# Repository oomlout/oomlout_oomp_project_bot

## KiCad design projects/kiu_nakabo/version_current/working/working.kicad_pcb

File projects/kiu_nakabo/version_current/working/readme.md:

# nakabo by kiu  
This is a harvested standardized copy of a project from github.  
The original project can be found at:  
https://github.com/kiu/nakabo  
Please consult that link for additional, details, files, and license information.  
Note: It was auto harvested and if the original repo had more than one board file or anything out of the ordinary the files here are likely not representative.

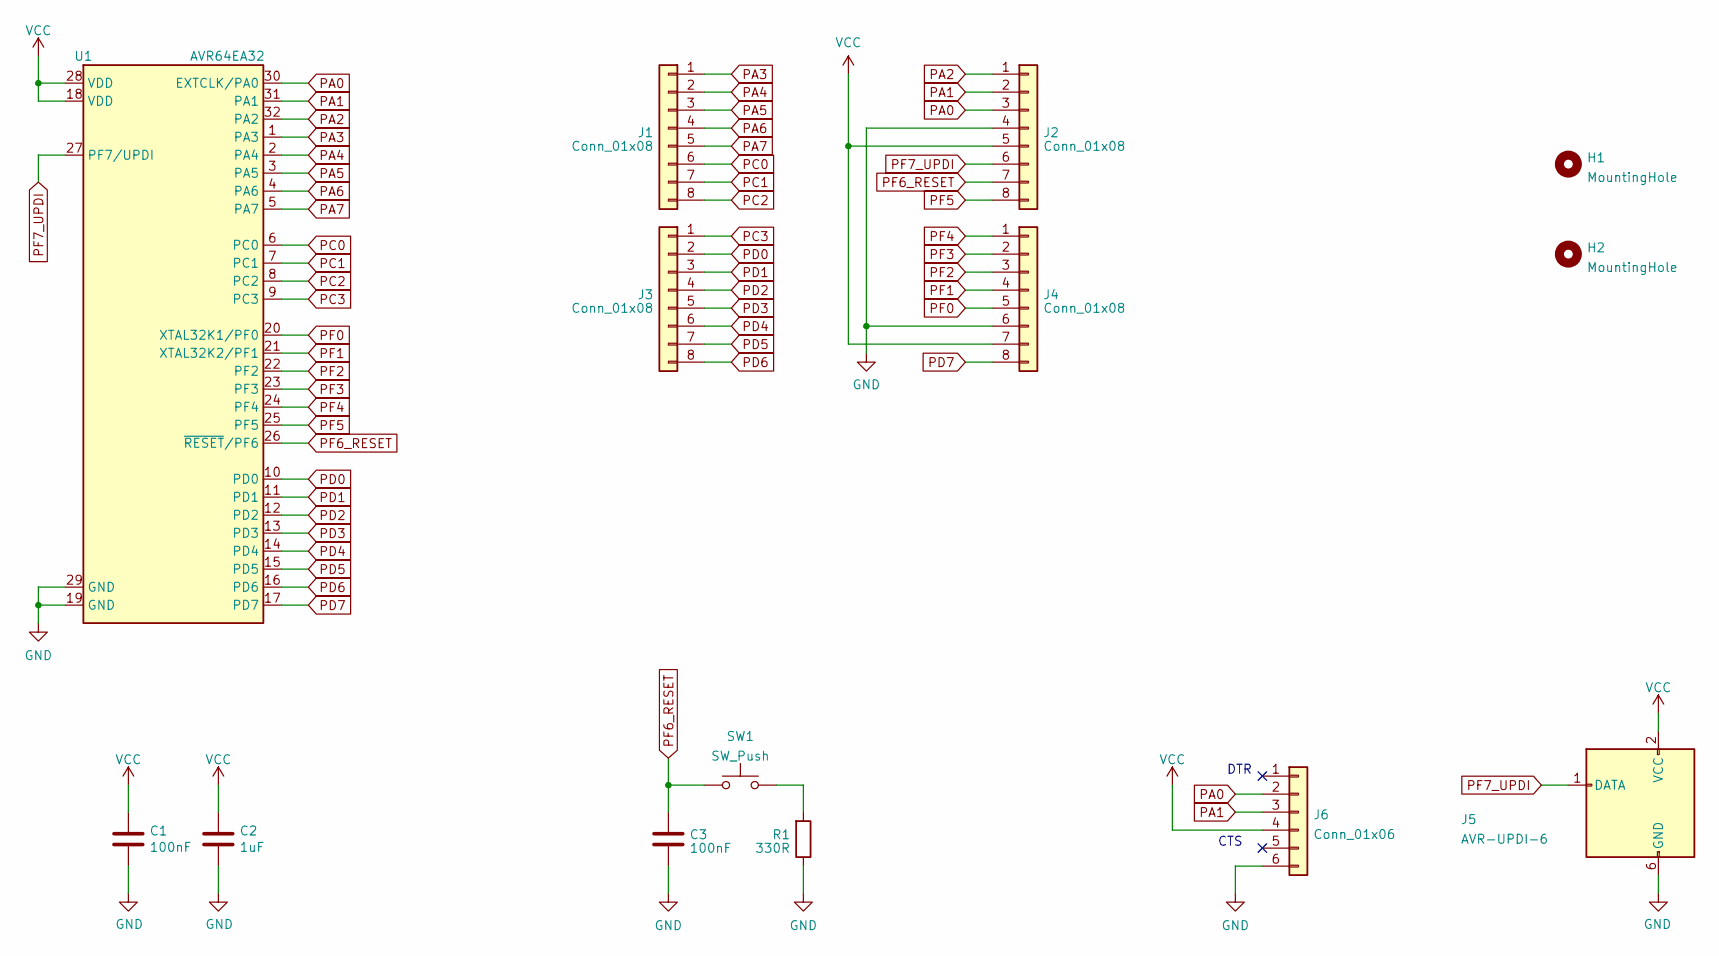
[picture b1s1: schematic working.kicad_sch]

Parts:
C1, C3: 100nF; C_0805_2012Metric
C2: 1uF; C_0805_2012Metric
H1, H2: MountingHole; MountingHole_3.2mm_M3_DIN965
J1, J2, J3, J4: Conn_01x08; PinSocket_1x08_P2.54mm_Vertical
J5: AVR-UPDI-6; IDC-Header_2x03_P2.54mm_Vertical
J6: Conn_01x06; PinSocket_1x06_P2.54mm_Vertical
R1: 330R; R_0805_2012Metric
SW1: SW_Push; SW_Push_1P1T_NO_4.5x4.5mm
U1: AVR64EA32; TQFP-32_7x7mm_P0.8mm

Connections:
GND: C1.2, C2.2, C3.2, J2.4, J4.6, J5.6 (GND), J6.6, R1.1, U1.19 (GND), U1.29 (GND)
unnamed: R1.2, SW1.2
PA0: J2.3, J6.2, U1.30 (EXTCLK/PA0)
PA1: J2.2, J6.3, U1.31 (PA1)
PA2: J2.1, U1.32 (PA2)
PA3: J1.1, U1.1 (PA3)
PA4: J1.2, U1.2 (PA4)
PA5: J1.3, U1.3 (PA5)
PA6: J1.4, U1.4 (PA6)
PA7: J1.5, U1.5 (PA7)
PC0: J1.6, U1.6 (PC0)
PC1: J1.7, U1.7 (PC1)
PC2: J1.8, U1.8 (PC2)
PC3: J3.1, U1.9 (PC3)
PD0: J3.2, U1.10 (PD0)
PD1: J3.3, U1.11 (PD1)
PD2: J3.4, U1.12 (PD2)
PD3: J3.5, U1.13 (PD3)
PD4: J3.6, U1.14 (PD4)
PD5: J3.7, U1.15 (PD5)
PD6: J3.8, U1.16 (PD6)
PD7: J4.8, U1.17 (PD7)
PF0: J4.5, U1.20 (XTAL32K1/PF0)
PF1: J4.4, U1.21 (XTAL32K2/PF1)
PF2: J4.3, U1.22 (PF2)
PF3: J4.2, U1.23 (PF3)
PF4: J4.1, U1.24 (PF4)
PF5: J2.8, U1.25 (PF5)
PF6_RESET: C3.1, J2.7, SW1.1, U1.26 (~RESET/PF6)
PF7_UPDI: J2.6, J5.1 (DATA), U1.27 (PF7/UPDI)
VCC: C1.1, C2.1, J2.5, J4.7, J5.2 (VCC), J6.4, U1.18 (VDD), U1.28 (VDD)

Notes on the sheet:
DTR
CTS

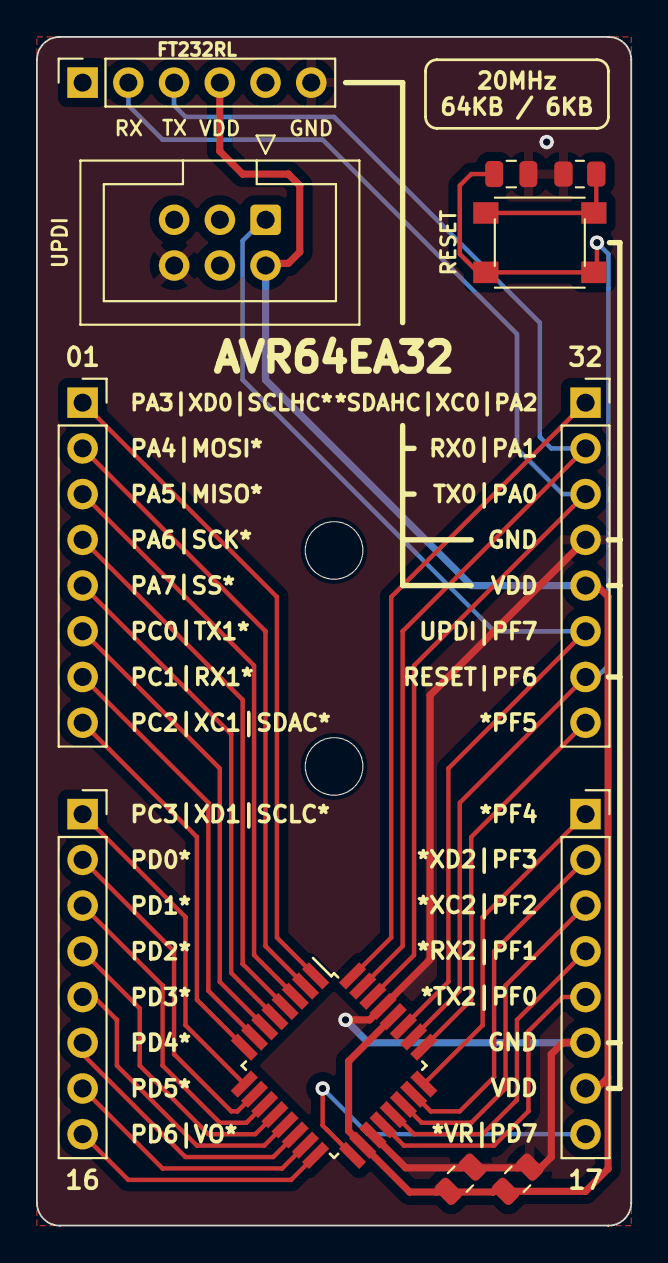
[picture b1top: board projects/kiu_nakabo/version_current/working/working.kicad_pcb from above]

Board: 2 copper layers, 33.0 x 66.0 mm, 14 parts (0 on the bottom side), 31 nets.

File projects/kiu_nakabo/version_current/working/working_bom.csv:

"Id";"Designator";"Footprint";"Quantity";"Designation";"Supplier and ref";
1;"J1,J4,J3,J2";"PinSocket_1x08_P2.54mm_Vertical";4;"Conn_01x08";;;
2;"J5";"IDC-Header_2x03_P2.54mm_Vertical";1;"AVR-UPDI-6";;;
3;"C2";"C_0805_2012Metric";1;"1uF";;;
4;"C3,C1";"C_0805_2012Metric";2;"100nF";;;
5;"H1,H2";"MountingHole_3.2mm_M3_DIN965";2;"MountingHole";;;
6;"U1";"TQFP-32_7x7mm_P0.8mm";1;"AVR64EA32";;;
7;"SW1";"SW_Push_1P1T_NO_4.5x4.5mm";1;"SW_Push";;;
8;"J6";"PinSocket_1x06_P2.54mm_Vertical";1;"Conn_01x06";;;
9;"R1";"R_0805_2012Metric";1;"330R";;;

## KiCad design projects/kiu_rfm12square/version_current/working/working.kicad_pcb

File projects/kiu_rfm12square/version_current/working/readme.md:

# rfm12square by kiu  
This is a harvested standardized copy of a project from github.  
The original project can be found at:  
https://github.com/kiu/rfm12square  
Please consult that link for additional, details, files, and license information.  
Note: It was auto harvested and if the original repo had more than one board file or anything out of the ordinary the files here are likely not representative.

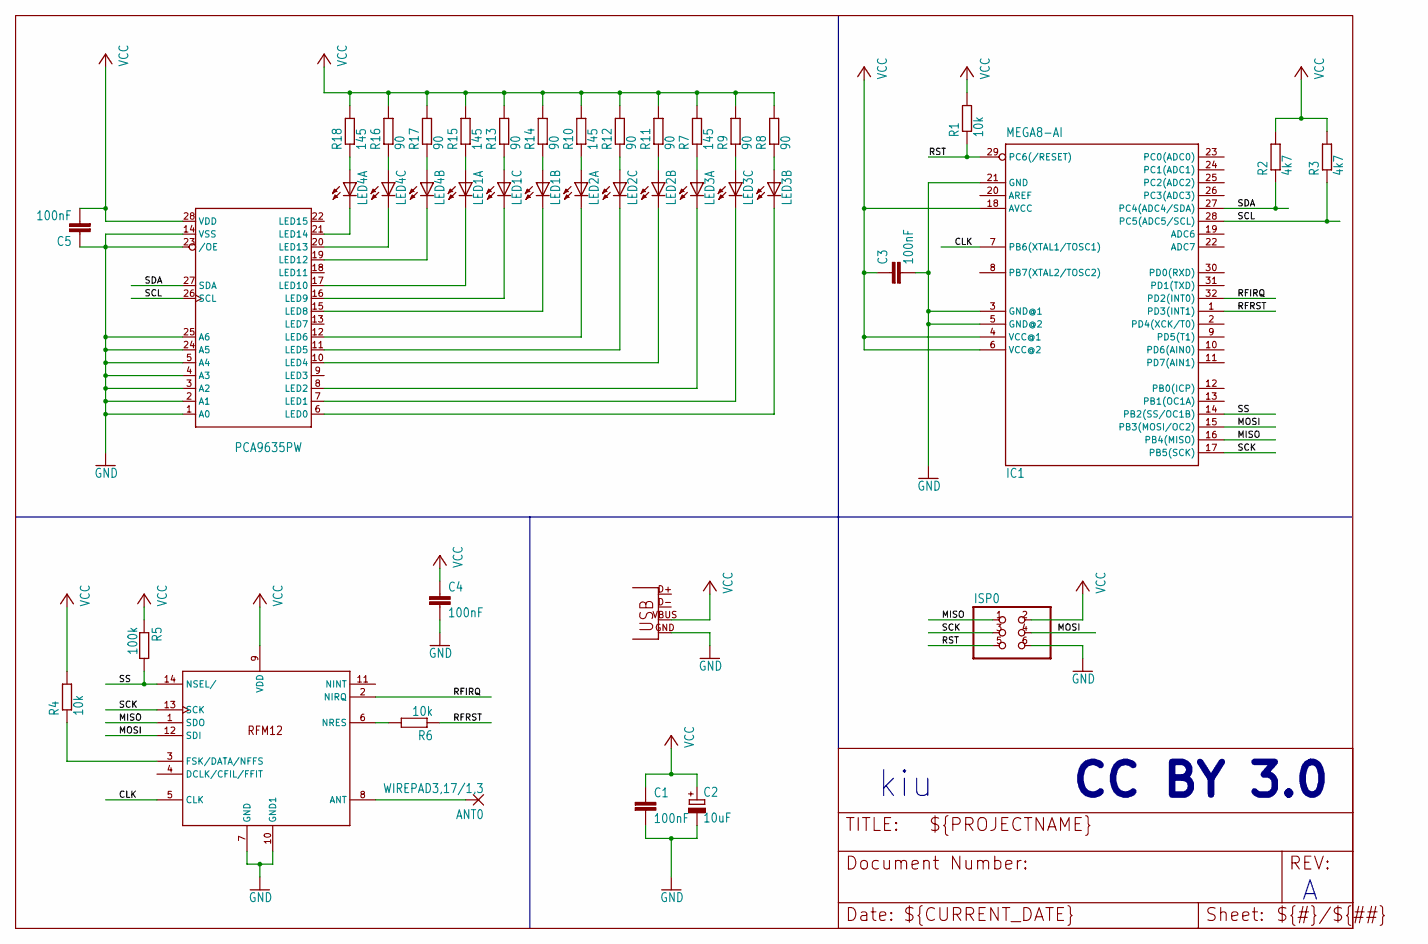
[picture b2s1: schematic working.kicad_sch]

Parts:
ANT0: WIREPAD3,17/1,3; 3,17_1,3
C1, C3, C4, C5: 100nF; C0603
C2: 10uF; CT3216
IC1: MEGA8-AI; TQFP32-08
IC2: PCA9635PW; TSSOP28
ISP0: PINHD-2X3; 2X03
LED1, LED2, LED3, LED4: MULTILED_LRTB_G6TG; P-LCC-6_TOPLED
R1, R4, R6: 10k; R0603
R2, R3: 4k7; R0603
R5: 100k; R0603
R7, R10, R15, R18: 145; R0603
R8, R9, R11, R12, R13, R14, R16, R17: 90; R0603
U$1: FRM12; RFM12
X1: USB-MICROB

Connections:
CLK: IC1.7 (PB6(XTAL1/TOSC1)), U$1.5 (CLK)
GND: C1.2, C2.-, C3.2, C4.2, C5.1, IC1.3 (GND@1), IC1.5 (GND@2), IC1.21 (GND), IC2.1 (A0), IC2.2 (A1), IC2.3 (A2), IC2.4 (A3), IC2.5 (A4), IC2.14 (VSS), IC2.23 (/OE), IC2.24 (A5), IC2.25 (A6), ISP0.6, U$1.7 (GND), U$1.10 (GND1), X1.GND
MISO: IC1.16 (PB4(MISO)), ISP0.1, U$1.1 (SDO)
MOSI: IC1.15 (PB3(MOSI/OC2)), ISP0.4, U$1.12 (SDI)
unnamed: LED4.A2 (A), R17.1
unnamed: LED1.A2 (A), R14.1
unnamed: LED4.A3 (A), R16.1
unnamed: LED4.A1 (A), R18.1
unnamed: LED1.A3 (A), R13.1
unnamed: IC2.6 (LED0), LED3.C2 (C)
unnamed: IC2.7 (LED1), LED3.C3 (C)
unnamed: IC2.8 (LED2), LED3.C1 (C)
unnamed: IC2.10 (LED4), LED2.C2 (C)
unnamed: IC2.11 (LED5), LED2.C3 (C)
unnamed: IC2.12 (LED6), LED2.C1 (C)
unnamed: IC2.15 (LED8), LED1.C2 (C)
unnamed: R4.1, U$1.3 (FSK/DATA/NFFS)
unnamed: R6.2, U$1.6 (NRES)
unnamed: LED1.A1 (A), R15.1
unnamed: ANT0.1, U$1.8 (ANT)
unnamed: IC2.16 (LED9), LED1.C3 (C)
unnamed: IC2.17 (LED10), LED1.C1 (C)
unnamed: LED2.A3 (A), R12.1
unnamed: IC2.19 (LED12), LED4.C2 (C)
unnamed: IC2.20 (LED13), LED4.C3 (C)
unnamed: IC2.21 (LED14), LED4.C1 (C)
unnamed: LED2.A2 (A), R11.1
unnamed: LED2.A1 (A), R10.1
unnamed: LED3.A1 (A), R7.1
unnamed: LED3.A3 (A), R9.1
unnamed: LED3.A2 (A), R8.1
RFIRQ: IC1.32 (PD2(INT0)), U$1.2 (NIRQ)
RFRST: IC1.1 (PD3(INT1)), R6.1
RST: IC1.29 (PC6(/RESET)), ISP0.5, R1.1
SCK: IC1.17 (PB5(SCK)), ISP0.3, U$1.13 (SCK)
SCL: IC1.28 (PC5(ADC5/SCL)), IC2.26 (SCL), R3.1
SDA: IC1.27 (PC4(ADC4/SDA)), IC2.27 (SDA), R2.1
SS: IC1.14 (PB2(SS/OC1B)), R5.2, U$1.14 (NSEL/)
VCC: C1.1, C2.+, C3.1, C4.1, C5.2, IC1.4 (VCC@1), IC1.6 (VCC@2), IC1.18 (AVCC), IC2.28 (VDD), ISP0.2, R1.2, R2.2, R3.2, R4.2, R5.1, R7.2, R8.2, R9.2, R10.2, R11.2, R12.2, R13.2, R14.2, R15.2, R16.2, R17.2, R18.2, U$1.9 (VDD), X1.VBUS

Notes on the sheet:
CC BY 3.0
kiu

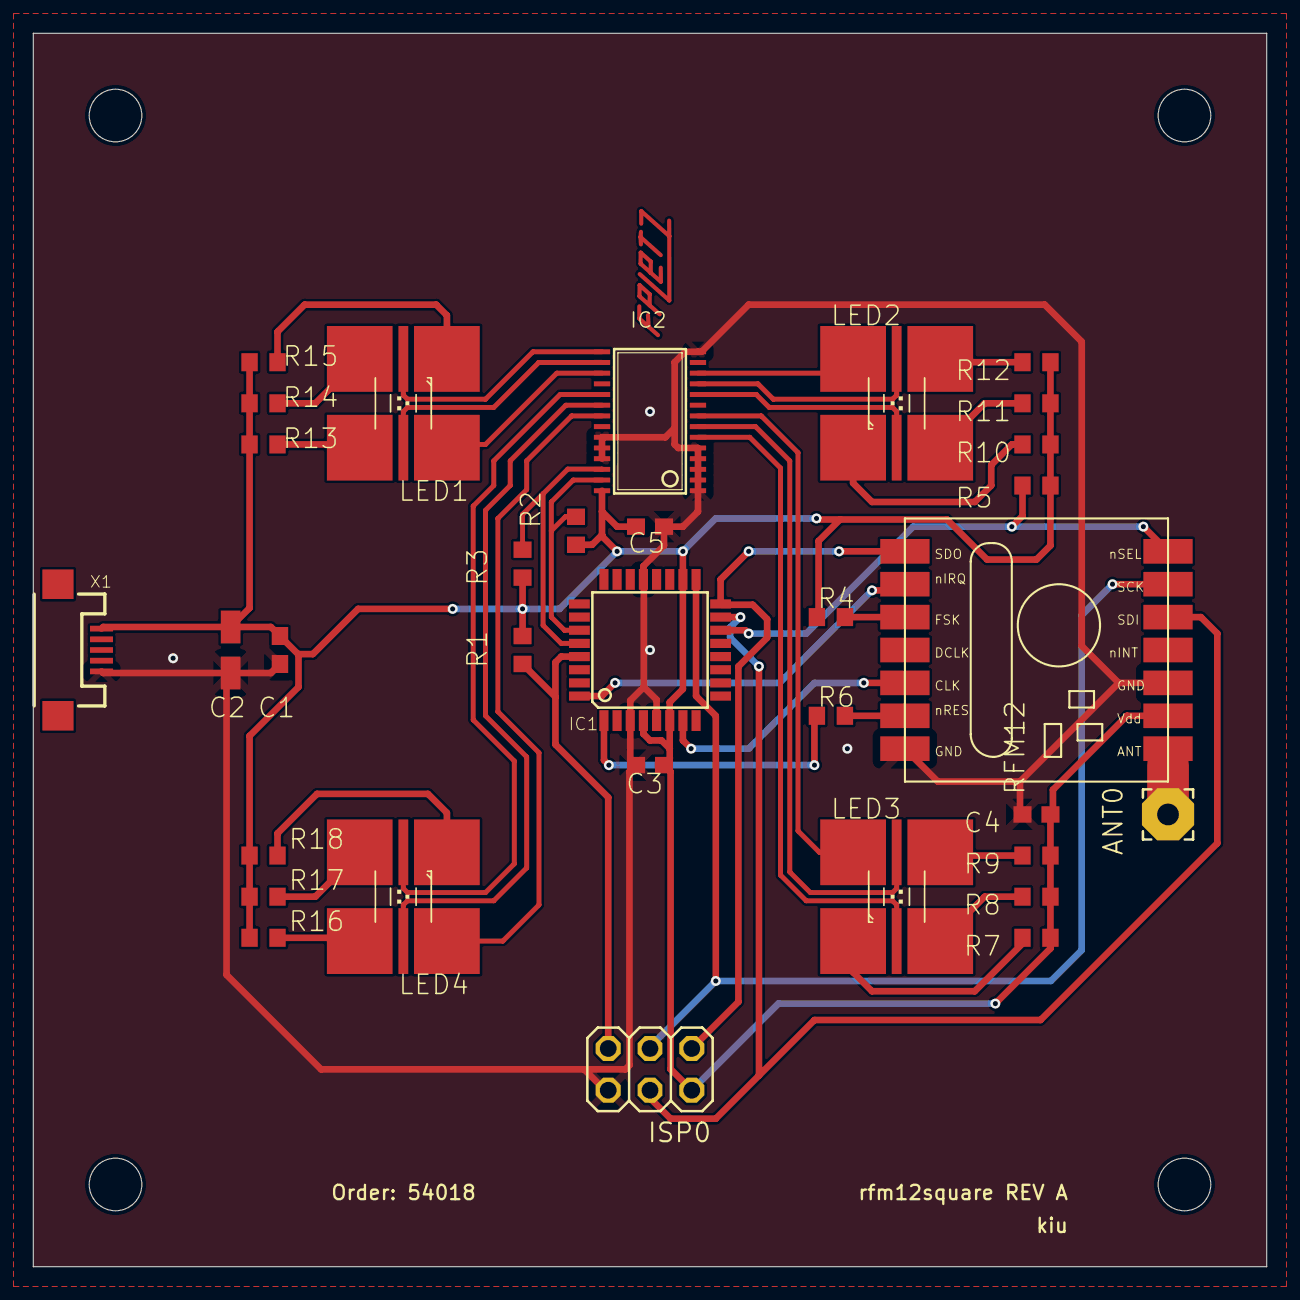
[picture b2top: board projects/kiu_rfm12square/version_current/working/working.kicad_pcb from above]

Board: 2 copper layers, 75.0 x 75.0 mm, 37 parts (0 on the bottom side), 39 nets.

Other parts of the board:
@HOLE0, @HOLE1, @HOLE2, @HOLE3: (no value)

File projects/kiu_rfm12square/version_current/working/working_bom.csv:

"Id";"Designator";"Footprint";"Quantity";"Designation";"Supplier and ref";
1;"@HOLE2,@HOLE1,@HOLE3,@HOLE0";"";4;"";;;
2;"LED1,LED3,LED4,LED2";"P-LCC-6_TOPLED";4;"MULTILED_LRTB_G6TG";;;
3;"R7,R18,R15,R10";"R0603";4;"145";;;
4;"C5,C3,C1,C4";"C0603";4;"100nF";;;
5;"R1,R6,R4";"R0603";3;"10k";;;
6;"R3,R2";"R0603";2;"4k7";;;
7;"U$1";"RFM12";1;"FRM12";;;
8;"ISP0";"2X03";1;"";;;
9;"IC2";"TSSOP28";1;"PCA9635PW";;;
10;"R14,R17,R11,R12,R13,R9,R16,R8";"R0603";8;"90";;;
11;"X1";"USB-MICROB";1;"USB-MICROB";;;
12;"R5";"R0603";1;"100k";;;
13;"IC1";"TQFP32-08";1;"MEGA8-AI";;;
14;"C2";"CT3216";1;"10uF";;;
15;"ANT0";"3,17_1,3";1;"WIREPAD3,17/1,3";;;

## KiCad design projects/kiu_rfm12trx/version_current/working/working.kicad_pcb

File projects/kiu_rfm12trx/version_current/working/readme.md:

# rfm12trx by kiu  
This is a harvested standardized copy of a project from github.  
The original project can be found at:  
https://github.com/kiu/rfm12trx  
Please consult that link for additional, details, files, and license information.  
Note: It was auto harvested and if the original repo had more than one board file or anything out of the ordinary the files here are likely not representative.

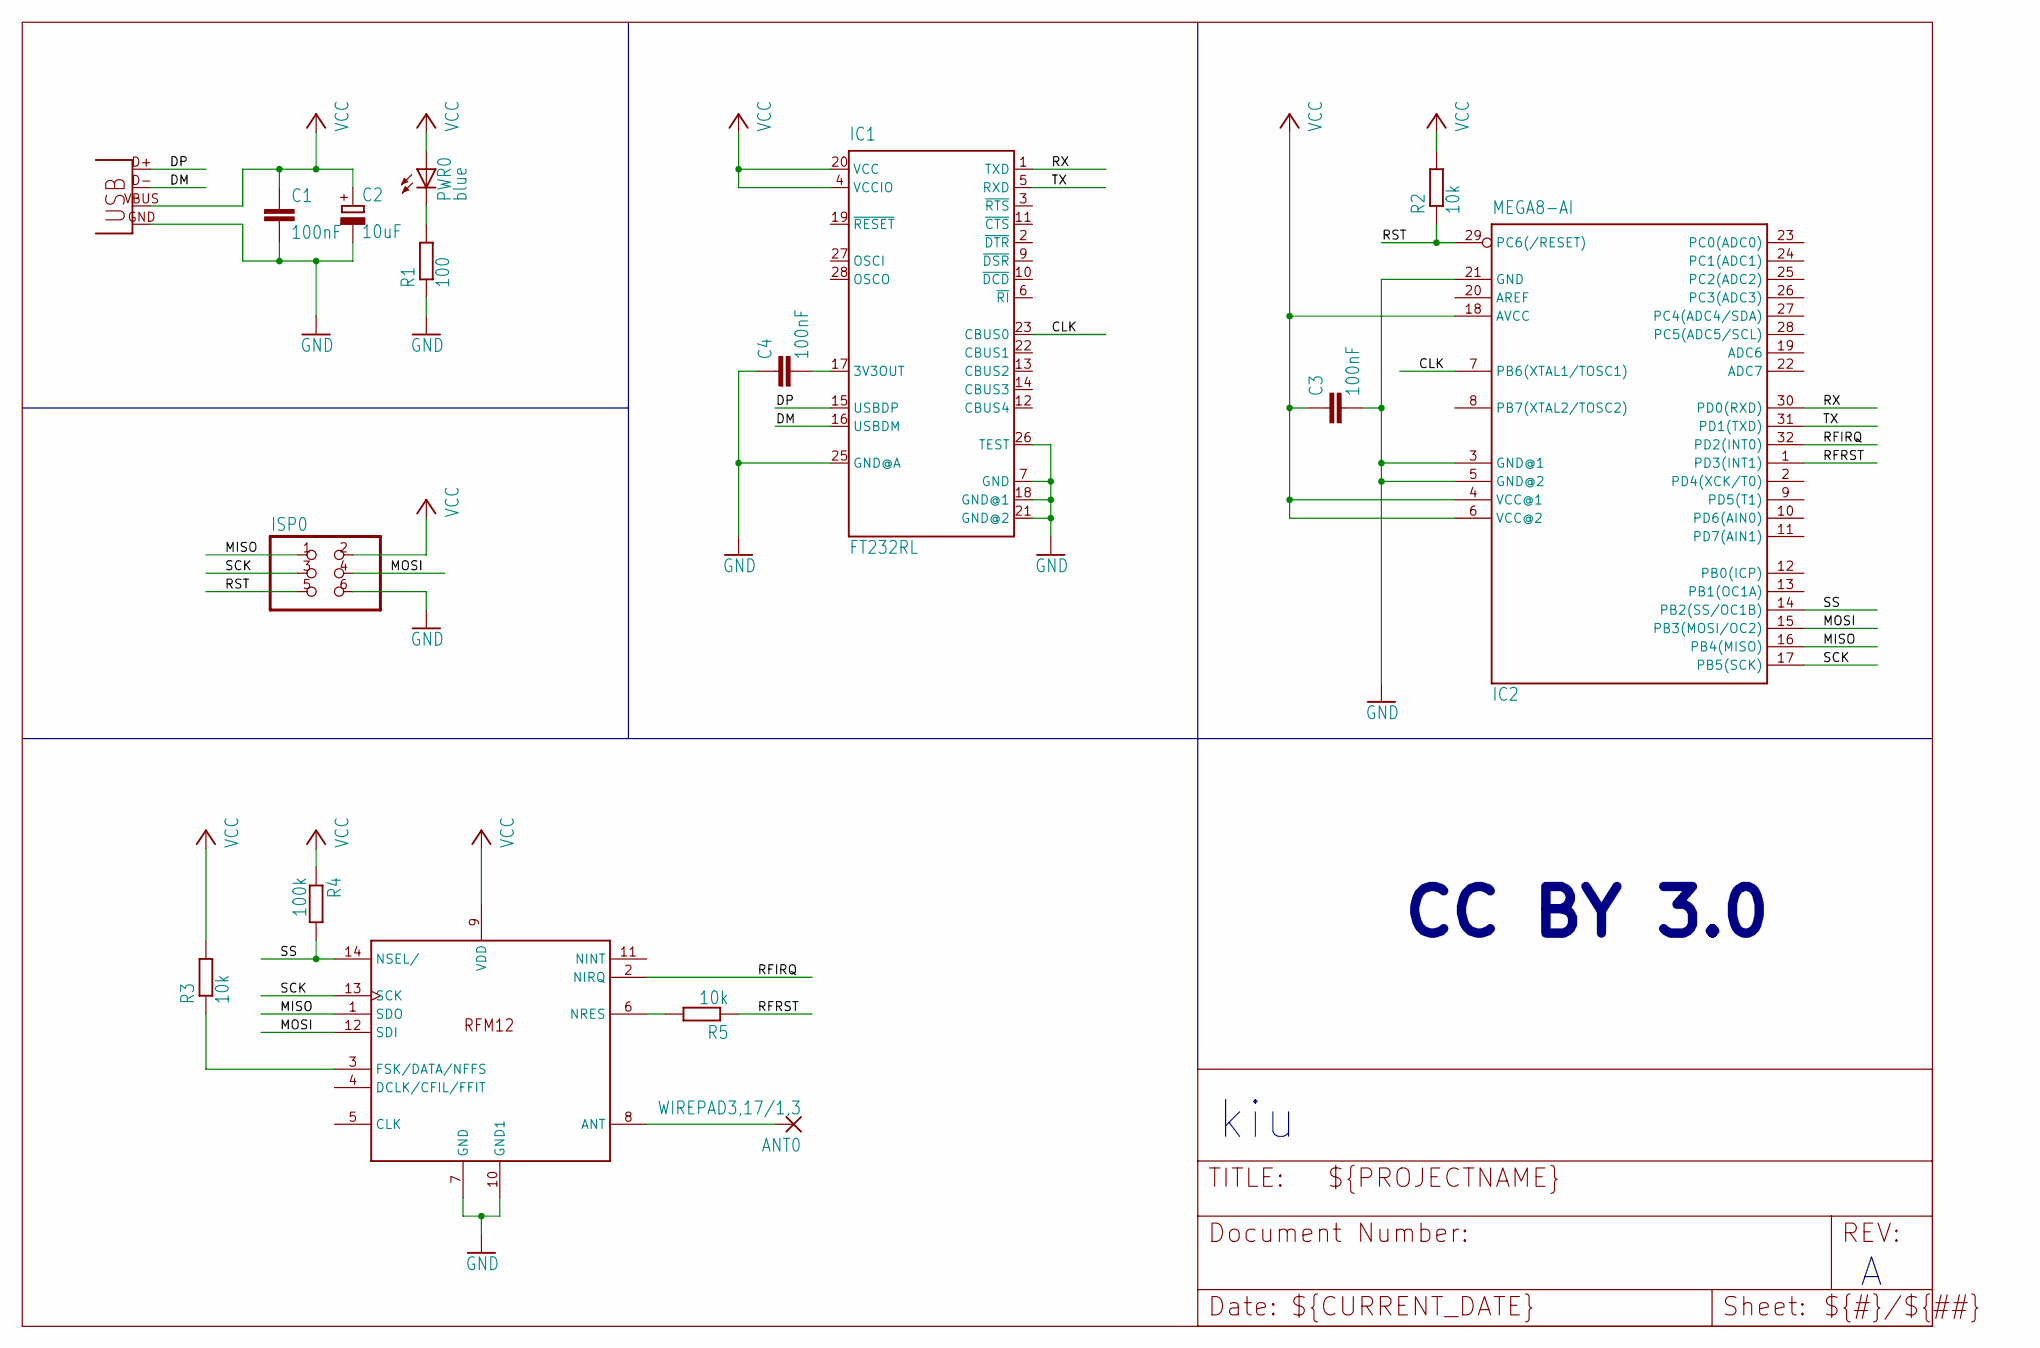
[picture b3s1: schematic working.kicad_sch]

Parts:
ANT0: WIREPAD3,17/1,3; 3,17_1,3
C1, C3, C4: 100nF; C0603
C2: 10uF; CT3216
IC1: FT232RL; SSOP28
IC2: MEGA8-AI; TQFP32-08
ISP0: PINHD-2X3; 2X03
PWR0: blue; CHIP-LED0805
R1: 100; R0603
R2, R3, R5: 10k; R0603
R4: 100k; R0603
U$1: FRM12; RFM12
X1: USB-MICROB

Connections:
CLK: IC1.23 (CBUS0), IC2.7 (PB6(XTAL1/TOSC1))
DM: IC1.16 (USBDM), X1.D-
DP: IC1.15 (USBDP), X1.D+
GND: C1.2, C2.-, C3.2, C4.1, IC1.7 (GND), IC1.18 (GND@1), IC1.21 (GND@2), IC1.25 (GND@A), IC1.26 (TEST), IC2.3 (GND@1), IC2.5 (GND@2), IC2.21 (GND), ISP0.6, R1.1, U$1.7 (GND), U$1.10 (GND1), X1.GND
MISO: IC2.16 (PB4(MISO)), ISP0.1, U$1.1 (SDO)
MOSI: IC2.15 (PB3(MOSI/OC2)), ISP0.4, U$1.12 (SDI)
unnamed: PWR0.C, R1.2
unnamed: C4.2, IC1.17 (3V3OUT)
unnamed: R3.1, U$1.3 (FSK/DATA/NFFS)
unnamed: R5.2, U$1.6 (NRES)
unnamed: ANT0.1, U$1.8 (ANT)
RFIRQ: IC2.32 (PD2(INT0)), U$1.2 (NIRQ)
RFRST: IC2.1 (PD3(INT1)), R5.1
RST: IC2.29 (PC6(/RESET)), ISP0.5, R2.1
RX: IC1.1 (TXD), IC2.30 (PD0(RXD))
SCK: IC2.17 (PB5(SCK)), ISP0.3, U$1.13 (SCK)
SS: IC2.14 (PB2(SS/OC1B)), R4.2, U$1.14 (NSEL/)
TX: IC1.5 (RXD), IC2.31 (PD1(TXD))
VCC: C1.1, C2.+, C3.1, IC1.4 (VCCIO), IC1.20 (VCC), IC2.4 (VCC@1), IC2.6 (VCC@2), IC2.18 (AVCC), ISP0.2, PWR0.A, R2.2, R3.2, R4.1, U$1.9 (VDD), X1.VBUS

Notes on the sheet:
kiu
CC BY 3.0

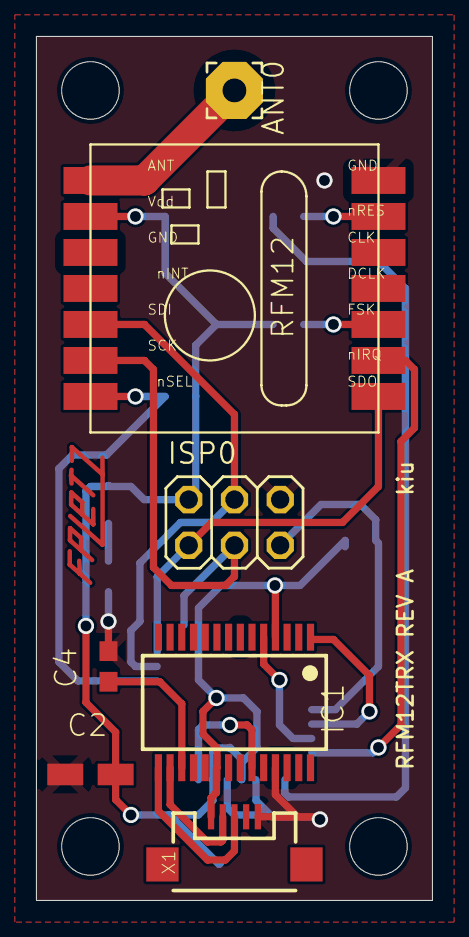
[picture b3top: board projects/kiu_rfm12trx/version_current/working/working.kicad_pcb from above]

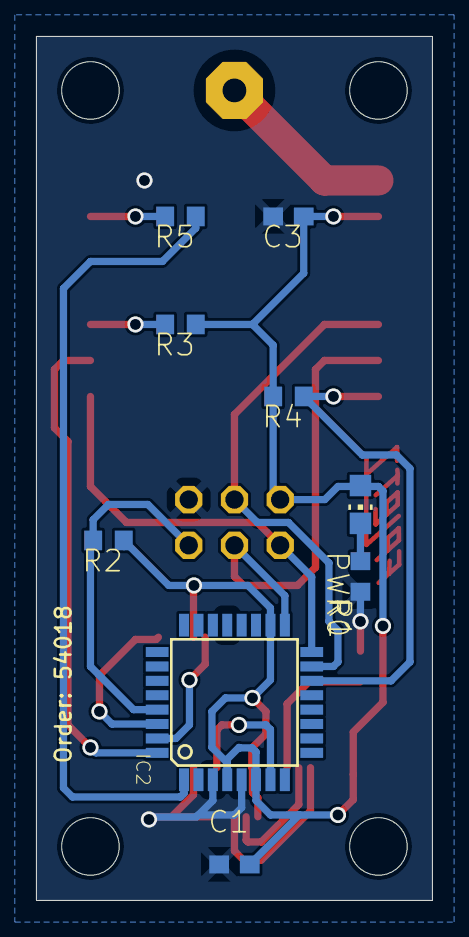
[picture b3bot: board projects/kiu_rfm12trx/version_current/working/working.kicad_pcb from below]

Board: 2 copper layers, 22.0 x 48.0 mm, 20 parts (9 on the bottom side), 19 nets.

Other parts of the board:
@HOLE0, @HOLE1, @HOLE2, @HOLE3: (no value)

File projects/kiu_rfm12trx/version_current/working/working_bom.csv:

"Id";"Designator";"Footprint";"Quantity";"Designation";"Supplier and ref";
1;"X1";"USB-MICROB";1;"USB-MICROB";;;
2;"@HOLE2,@HOLE0,@HOLE1,@HOLE3";"";4;"";;;
3;"C4,C1,C3";"C0603";3;"100nF";;;
4;"IC1";"SSOP28";1;"FT232RL";;;
5;"C2";"CT3216";1;"10uF";;;
6;"ANT0";"3,17_1,3";1;"WIREPAD3,17/1,3";;;
7;"ISP0";"2X03";1;"";;;
8;"U$1";"RFM12";1;"FRM12";;;
9;"R3,R5,R2";"R0603";3;"10k";;;
10;"IC2";"TQFP32-08";1;"MEGA8-AI";;;
11;"R4";"R0603";1;"100k";;;
12;"R1";"R0603";1;"100";;;
13;"PWR0";"CHIP-LED0805";1;"blue";;;

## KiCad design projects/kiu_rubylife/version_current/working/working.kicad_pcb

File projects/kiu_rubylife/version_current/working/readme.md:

# OOMP Project  
## rubylife  by kiu  
  
oomp key: oomp_projects_flat_kiu_rubylife  
(snippet of original readme)  
  
- rubylife  
Show the world your ruby affection and live the [-BadgeLife](https://twitter.com/search?q=%23badgelife)!  

- What does it do?  
Besides being a stylish ruby pin, it can blink a few animations :)  
  
- What do I need?  
All you need is soldering gear (iron, tin, tweezers). Everything else is in the kit.  
  
-- I don't know how to solder!  
It's easier than it looks, but a bit of help to kickstart your hardware adventure doesn't hurt. Ask your colleagues or friends for help. Or seek help in a [hackerspace](https://hackaday.io/hackerspaces) near you, they will love to teach you the ropes!  
  
-- Anything I need to know before I start?  
Be aware that all parts - except for the resistors - have a polarity. Their orientation on the board is important.  
  
Checkout this [reference](https://github.com/kiu/rubylife/raw/master/media/rubylife_polarity.jpg)!  
  
-- What is in the kit?  
  
| Amount | Item |  
| ------ | ---- |  
| 1 | Printed circuit board |  
| 1 | Pre-programmed microcontroller |  
| 8 | Red LED |  
| 8 | Resistors |  
| 1 | Capacitor |  
| 1 | Battery Holder |  
| 1 | Battery |  
| 1 | Mounting pin |  
| 1 | Glue dot |  
  
A more detailed description can be found in the [Bill-Of-Materials](https://github.com/kiu/rubylife/raw/master/bom.pdf)  
  
- I want to write my own software  
Easy, but be aware that you need C skills to proceed :/  
  
1. Setup an ATTiny development environment, e.g. [Atmel Studio](https://www.microchip.co  
  full source readme at [readme_src.md](readme_src.md)  
  
source repo at: [https://github.com/kiu/rubylife](https://github.com/kiu/rubylife)  
## Board  

## Schematic  

[schematic pdf](working_schematic.pdf)  
## Images

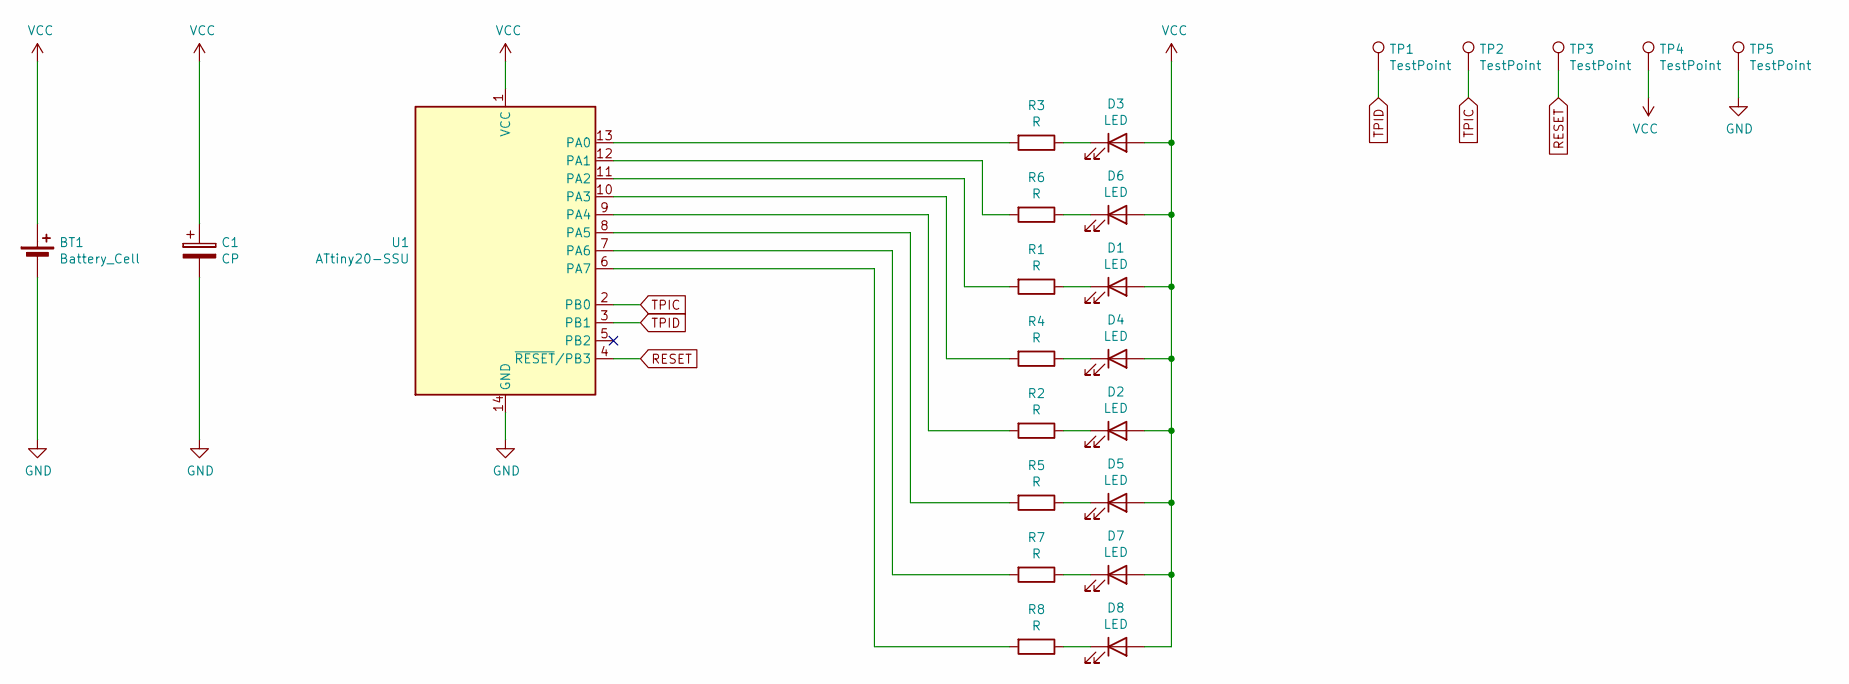
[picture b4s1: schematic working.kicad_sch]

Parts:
BT1: Battery_Cell; CR2032 SMD
C1: CP; CP_Tantalum_Case-B_EIA-3528-21_Hand
D1, D2, D3, D4, D5, D6, D7, D8: LED; LED_1206
R1, R2, R3, R4, R5, R6, R7, R8: R; R_1206
TP1, TP2, TP3, TP4, TP5: TestPoint; Measurement_Point_Round-SMD-Pad_Small
U1: ATtiny20-SSU; SOIC-14_3.9x8.7mm_Pitch1.27mm

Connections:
GND: BT1.2 (-), C1.2, TP5.1, U1.14 (GND)
unnamed: D1.1 (K), R1.1
unnamed: D2.1 (K), R2.1
unnamed: D3.1 (K), R3.1
unnamed: D4.1 (K), R4.1
unnamed: D5.1 (K), R5.1
unnamed: D6.1 (K), R6.1
unnamed: D7.1 (K), R7.1
unnamed: D8.1 (K), R8.1
unnamed: R1.2, U1.11 (PA2)
unnamed: R2.2, U1.9 (PA4)
unnamed: R3.2, U1.13 (PA0)
unnamed: R4.2, U1.10 (PA3)
unnamed: R5.2, U1.8 (PA5)
unnamed: R6.2, U1.12 (PA1)
unnamed: R7.2, U1.7 (PA6)
unnamed: R8.2, U1.6 (PA7)
RESET: TP3.1, U1.4 (~RESET/PB3)
TPIC: TP2.1, U1.2 (PB0)
TPID: TP1.1, U1.3 (PB1)
VCC: BT1.1 (+), C1.1, D1.2 (A), D2.2 (A), D3.2 (A), D4.2 (A), D5.2 (A), D6.2 (A), D7.2 (A), D8.2 (A), TP4.1, U1.1 (VCC)

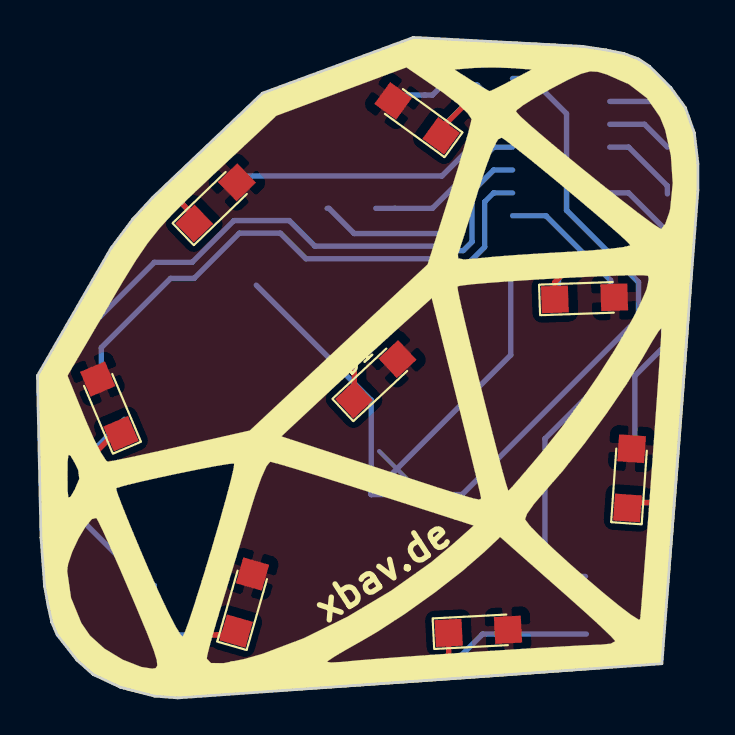
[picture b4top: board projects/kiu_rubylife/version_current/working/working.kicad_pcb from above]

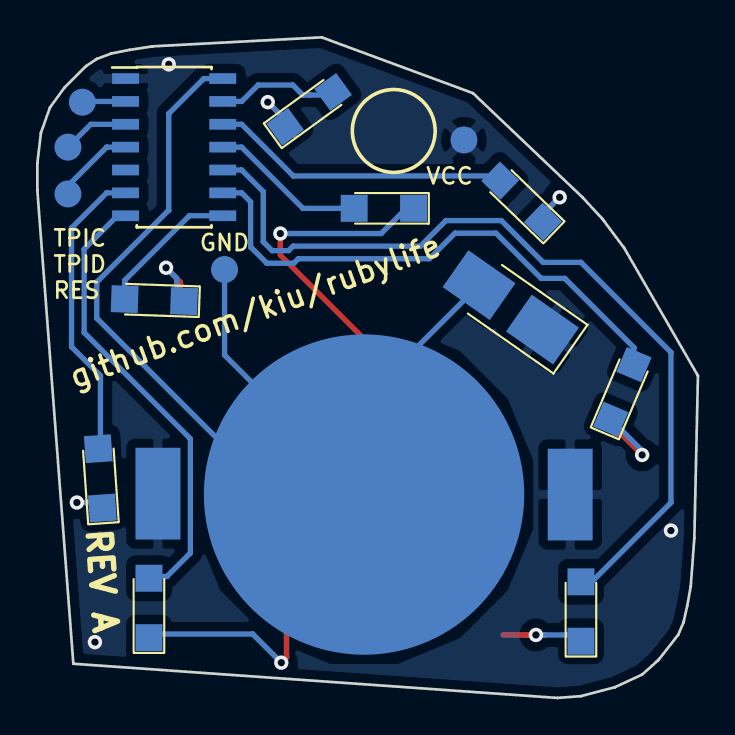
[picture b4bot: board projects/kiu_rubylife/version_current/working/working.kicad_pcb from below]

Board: 2 copper layers, 36.7 x 36.7 mm, 24 parts (16 on the bottom side), 21 nets.

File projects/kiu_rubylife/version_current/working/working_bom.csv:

"Id";"Designator";"Footprint";"Quantity";"Designation";"Supplier and ref";
1;"BT1";"CR2032 SMD";1;"Battery_Cell";;;
2;"U1";"SOIC-14_3.9x8.7mm_Pitch1.27mm";1;"ATtiny20-SSU";;;
3;"G***";"Ruby";1;"RUBY";;;
4;"C1";"CP_Tantalum_Case-B_EIA-3528-21_Hand";1;"CP";;;
5;"D1,D2,D3,D4,D5,D6,D7,D8";"LED_1206";8;"LED";;;
6;"R1,R2,R3,R4,R5,R6,R7,R8";"R_1206";8;"R";;;

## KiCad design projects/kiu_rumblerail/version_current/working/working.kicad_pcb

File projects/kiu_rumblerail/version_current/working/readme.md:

# RumbleRail by kiu  
This is a harvested standardized copy of a project from github.  
The original project can be found at:  
https://github.com/kiu/RumbleRail  
Please consult that link for additional, details, files, and license information.  
Note: It was auto harvested and if the original repo had more than one board file or anything out of the ordinary the files here are likely not representative.

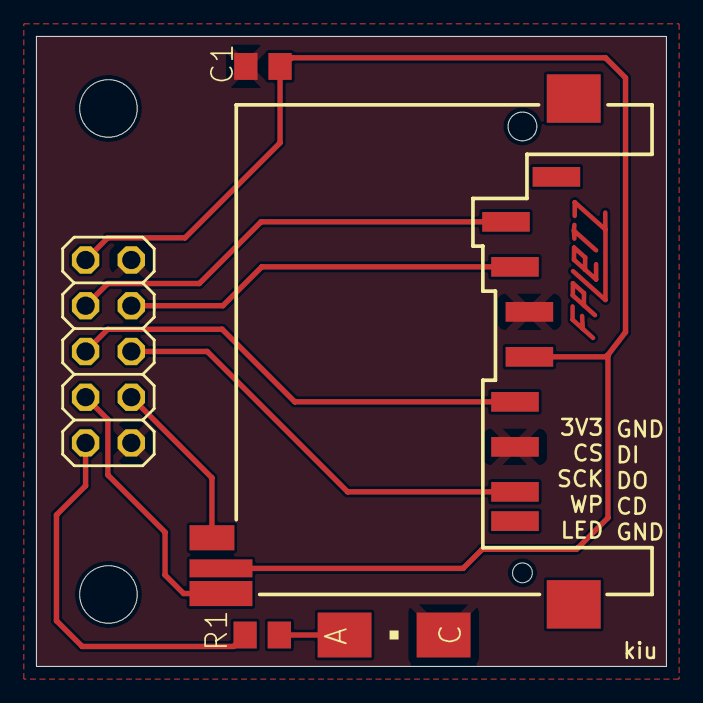
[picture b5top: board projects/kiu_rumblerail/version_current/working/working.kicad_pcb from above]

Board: 2 copper layers, 35.0 x 35.0 mm, 7 parts (0 on the bottom side), 10 nets.

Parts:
@HOLE0, @HOLE1: (no value)
C1: 100nF; C0805
JP1: 2X05
LED1: PLCC-2-NOTHERM
R1: R0805
SD1: FPS009-3001; FPS009-3000

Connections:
+3V3: C1.2, JP1.1, SD1.4, SD1.COM_TERM
CD: JP1.8, SD1.DETECT
CS: JP1.3, SD1.1
DI: JP1.4, SD1.2
DO: JP1.6, SD1.7
GND: C1.1, JP1.2, JP1.10, LED1.C, SD1.3, SD1.6
LED: JP1.9, R1.1
unnamed: LED1.A, R1.2
SCK: JP1.5, SD1.5
WP: JP1.7, SD1.WRITE_PROT

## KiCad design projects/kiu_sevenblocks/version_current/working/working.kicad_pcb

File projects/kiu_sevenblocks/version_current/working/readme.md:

# SevenBlocks by kiu  
This is a harvested standardized copy of a project from github.  
The original project can be found at:  
https://github.com/kiu/SevenBlocks  
Please consult that link for additional, details, files, and license information.  
Note: It was auto harvested and if the original repo had more than one board file or anything out of the ordinary the files here are likely not representative.

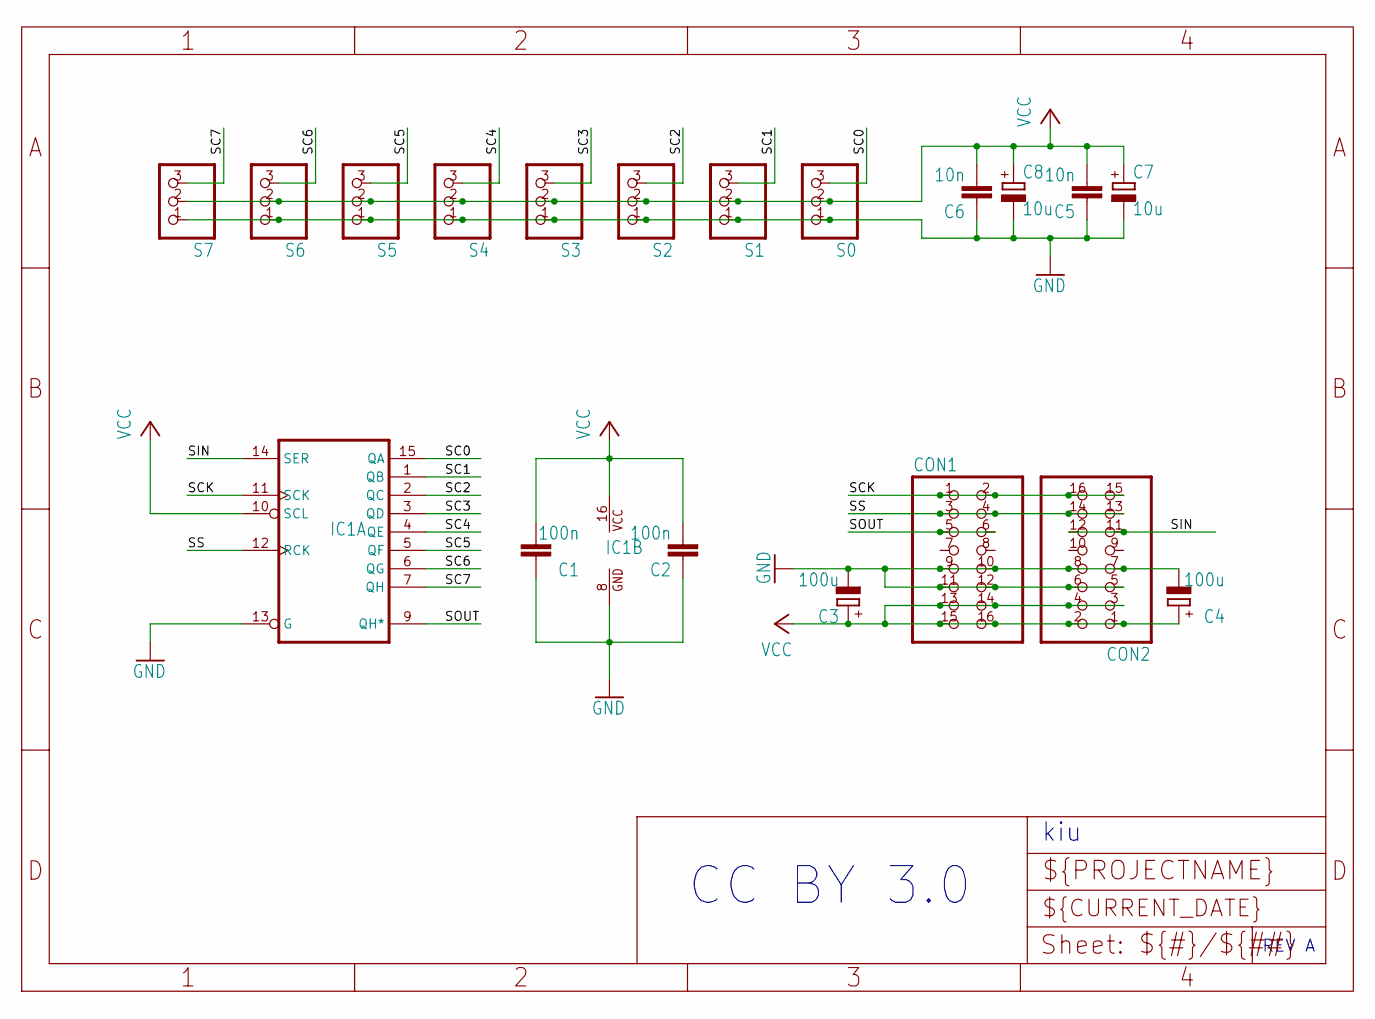
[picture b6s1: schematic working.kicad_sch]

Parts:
C1, C2: 100n; C0805
C3, C4: 100u; 153CLV-0505
C5, C6: 10n; C0805
C7, C8: 10u; 153CLV-0405
CON1, CON2: PINHD-2X8; 2X08
IC1: 74595D; SO16
S0, S1, S2, S3, S4, S5, S6, S7: PINHD-1X3; 1X03

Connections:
GND: C1.1, C2.1, C3.-, C4.-, C5.1, C6.1, C7.-, C8.-, CON1.9, CON1.10, CON1.11, CON1.12, CON2.5, CON2.6, CON2.7, CON2.8, IC1.8 (GND), IC1.13 (G), S0.1, S1.1, S2.1, S3.1, S4.1, S5.1, S6.1, S7.1
SC0: IC1.15 (QA), S0.3
SC1: IC1.1 (QB), S1.3
SC2: IC1.2 (QC), S2.3
SC3: IC1.3 (QD), S3.3
SC4: IC1.4 (QE), S4.3
SC5: IC1.5 (QF), S5.3
SC6: IC1.6 (QG), S6.3
SC7: IC1.7 (QH), S7.3
SCK: CON1.1, CON1.2, CON2.15, CON2.16, IC1.11 (SCK)
SIN: CON2.11, CON2.12, IC1.14 (SER)
SOUT: CON1.5, CON1.6, IC1.9 (QH*)
SS: CON1.3, CON1.4, CON2.13, CON2.14, IC1.12 (RCK)
VCC: C1.2, C2.2, C3.+, C4.+, C5.2, C6.2, C7.+, C8.+, CON1.13, CON1.14, CON1.15, CON1.16, CON2.1, CON2.2, CON2.3, CON2.4, IC1.10 (SCL), IC1.16 (VCC), S0.2, S1.2, S2.2, S3.2, S4.2, S5.2, S6.2, S7.2

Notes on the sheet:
CC BY 3.0
REV A
kiu

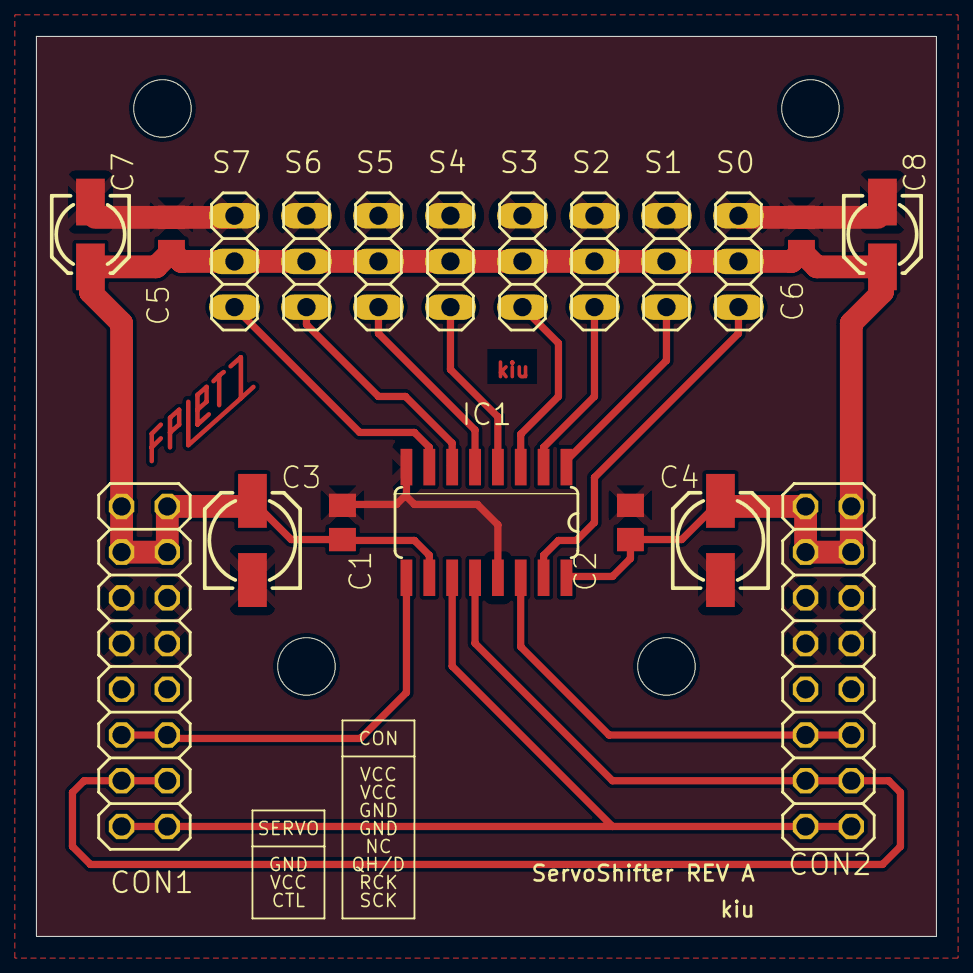
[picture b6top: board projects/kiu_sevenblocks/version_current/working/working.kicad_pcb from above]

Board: 2 copper layers, 50.0 x 50.0 mm, 23 parts (0 on the bottom side), 14 nets.

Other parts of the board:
@HOLE0, @HOLE1, @HOLE2, @HOLE3: (no value)

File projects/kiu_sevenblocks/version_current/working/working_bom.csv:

"Id";"Designator";"Footprint";"Quantity";"Designation";"Supplier and ref";
1;"C5,C6";"C0805";2;"10n";;;
2;"@HOLE1,@HOLE2,@HOLE3,@HOLE0";"";4;"";;;
3;"C3,C4";"153CLV-0505";2;"100u";;;
4;"S5,S2,S6,S3,S7,S4,S0,S1";"1X03";8;"";;;
5;"C7,C8";"153CLV-0405";2;"10u";;;
6;"C1,C2";"C0805";2;"100n";;;
7;"IC1";"SO16";1;"74HC595D";;;
8;"CON2,CON1";"2X08";2;"";;;
